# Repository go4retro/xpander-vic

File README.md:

# X-Pander VIC

## Introduction

Cousin to the X-Pander 3 for the C64/SX/C128/C128D, X-Pander VIC opens up a wealth of expansion options for your Commodore VIC-20/VIC-1001. This design continues on tradition of vintage designs like the CardCo Cardboard, while adding more granular controls over select lines like the CMD EX-3/EX2+1 for the C64. The X-Pander VIC offers the following features:

- Individually-selectable expansion ports
- sPower indicators for each port
- Ability to swap IO select lines ports
- Easily accessed piano-style configuration switches
- Top-loading or back-loading terminal port.
- Terminal port can accommodate 2 cartridges at the same time*
- Reset switch

\* Both top and back-loading options for terminal port share a single set of configuration switches, requiring 2 cartridges that can coexist without configuration.

## Requirements

- Commodore VIC-20 or VIC-1001

## Purchase

The current X-Pander VIC design is not yet available, but an older model (which requires some modification by the consumer can be purchased at the [RETRO Innovations Online Store](https://store.go4retro.com/non-functional-goodies/).

## Technical Details

X-Pander VIC creates a “passive” cartridge port “bus”, with switches on the following lines:

- Power (2 switches)
- IO2
- IO3
- RAM1
- RAM2
- RAM3
- BLK1
- BLK2
- BLK3
- BLK5
- AUDIO

Additionally, all ports except the first contain jumpers allowing one to “swap”  IO2 and IO3. This can be used to move a peripheral cartridge (like a  serial card or ethernet card) normally residing at IO3 to the  alternative IO3 position so that it can coexist with another IO cartridge. Jumpers are provided, but the jumper  pins can be removed and replaced with a subminiature DPDT (double pole,  double throw) switch.

## Support

Expansion port cartridges were not normally designed to coexist with  other cartridges. Thus, it is impossible to detail the nearly infinite  combinations and whether each works or not. Also, since the “bus”  places additional load on the unbuffered expansion port IO lines,  cartridges that are susceptible to signal degradation may not work with  X-Pander VIC, even when installed alone.

Some helpful hints:

- Always insert or remove X-Pander VIC with the system port off
- Clean cartridge contacts before installation
- Switches are “on” when depressed. Normally, all switches can be left in the “on” position
- IO2/IO3 swap jumpers must be moved as a pairs

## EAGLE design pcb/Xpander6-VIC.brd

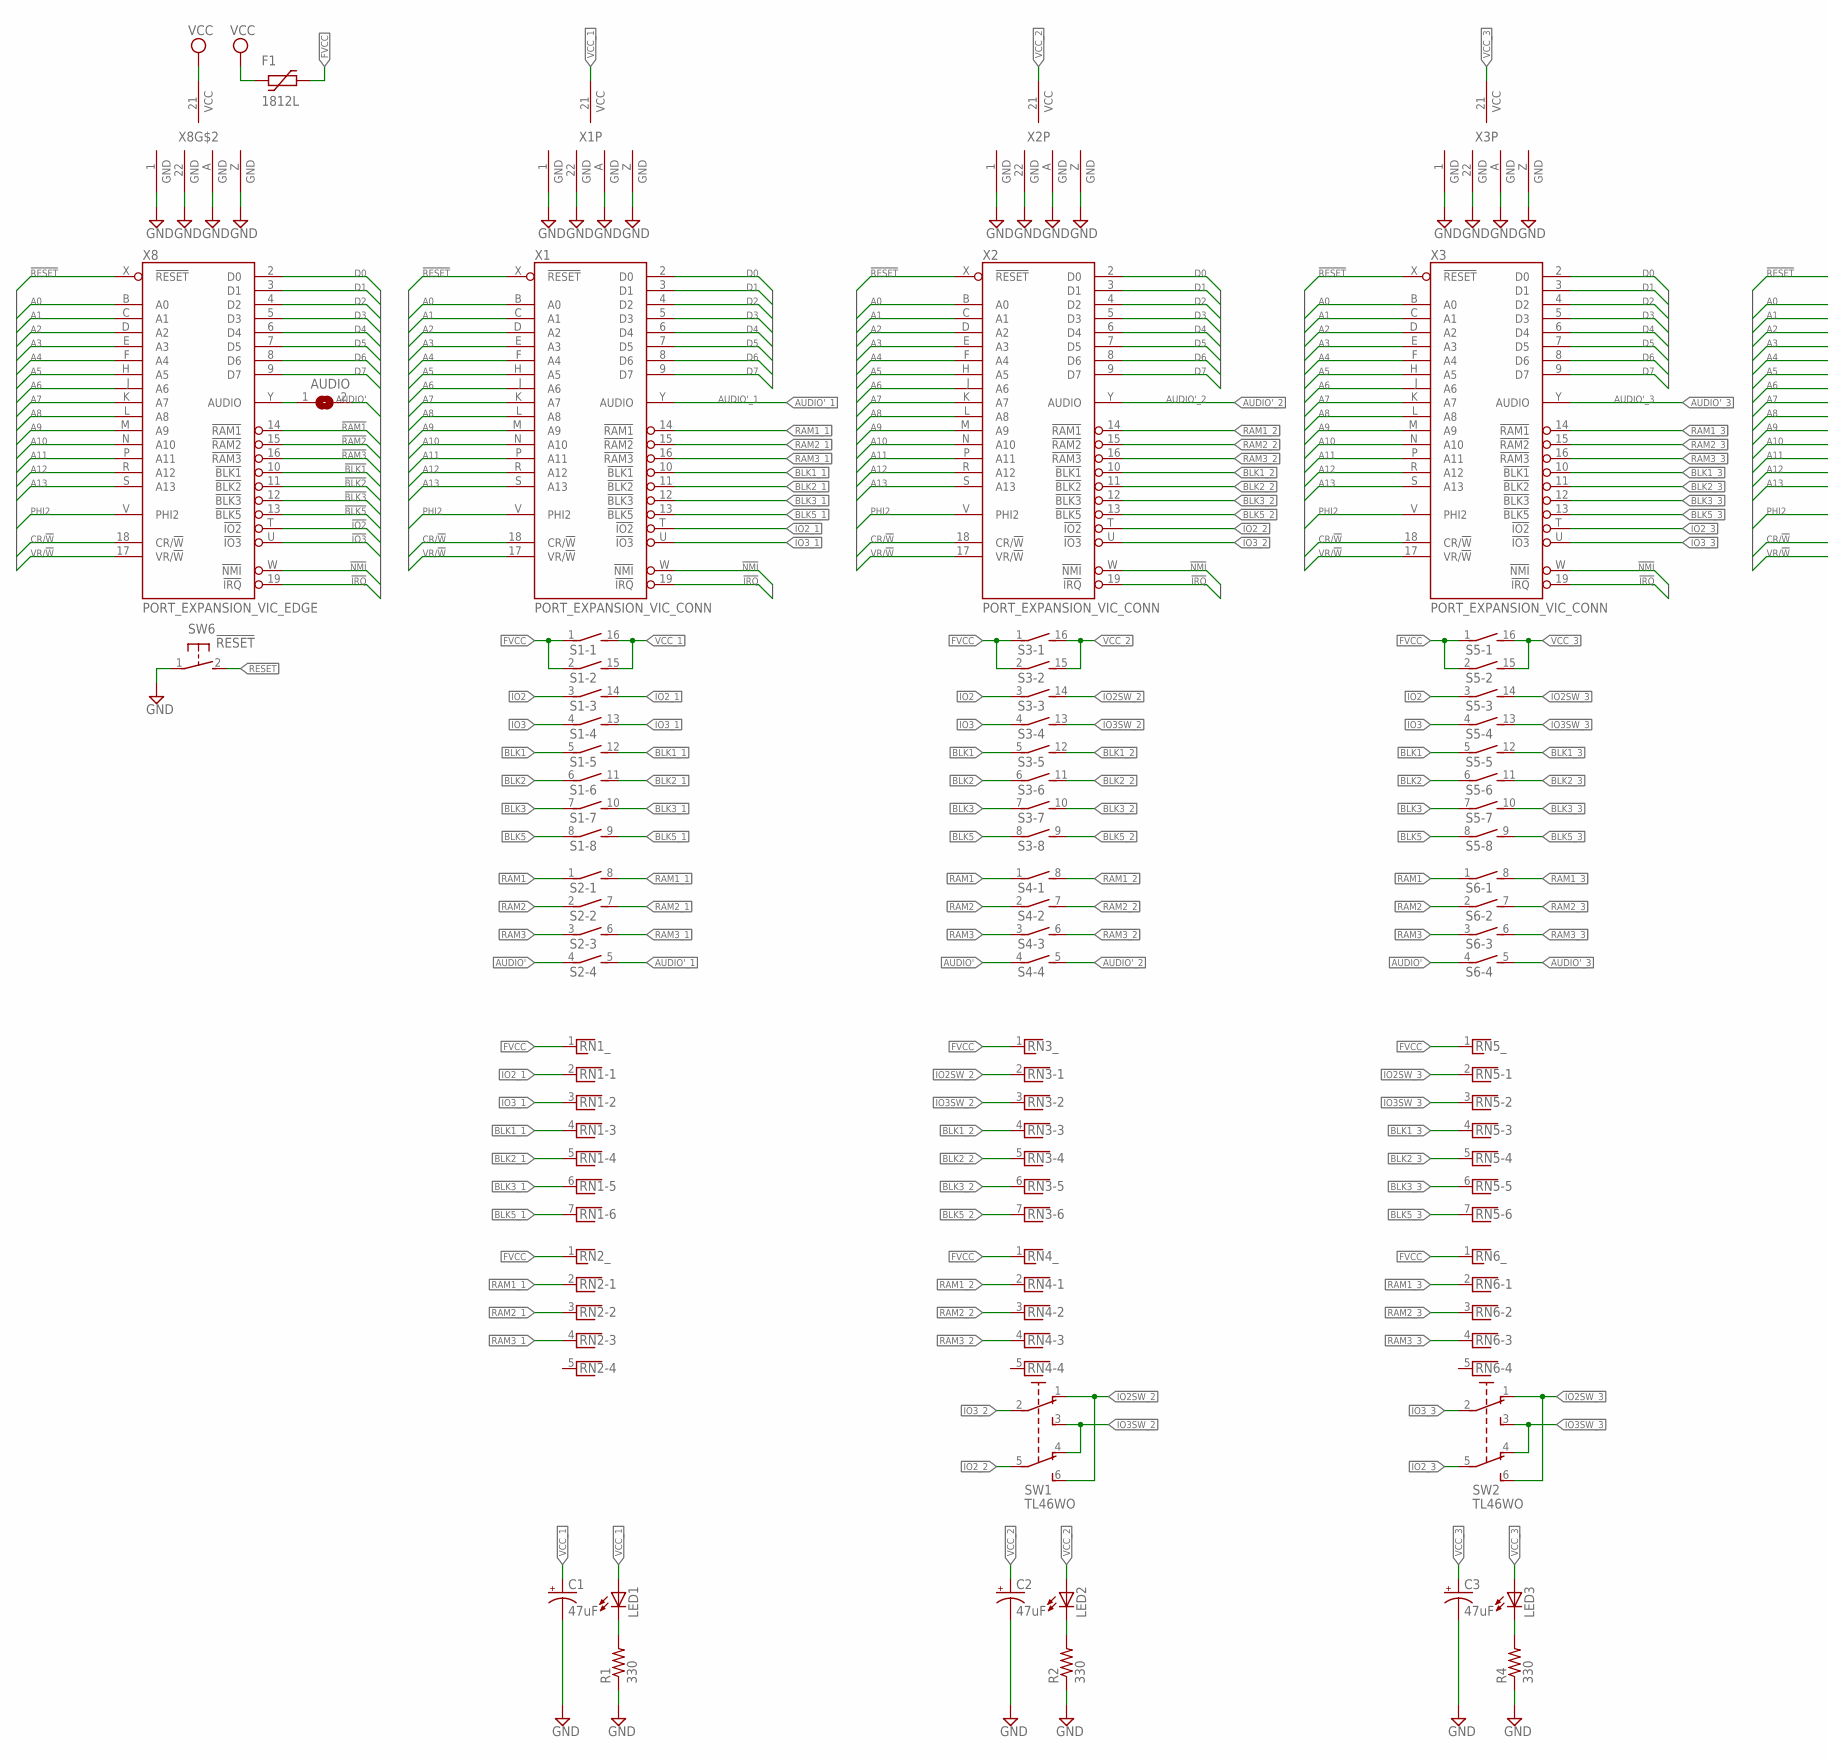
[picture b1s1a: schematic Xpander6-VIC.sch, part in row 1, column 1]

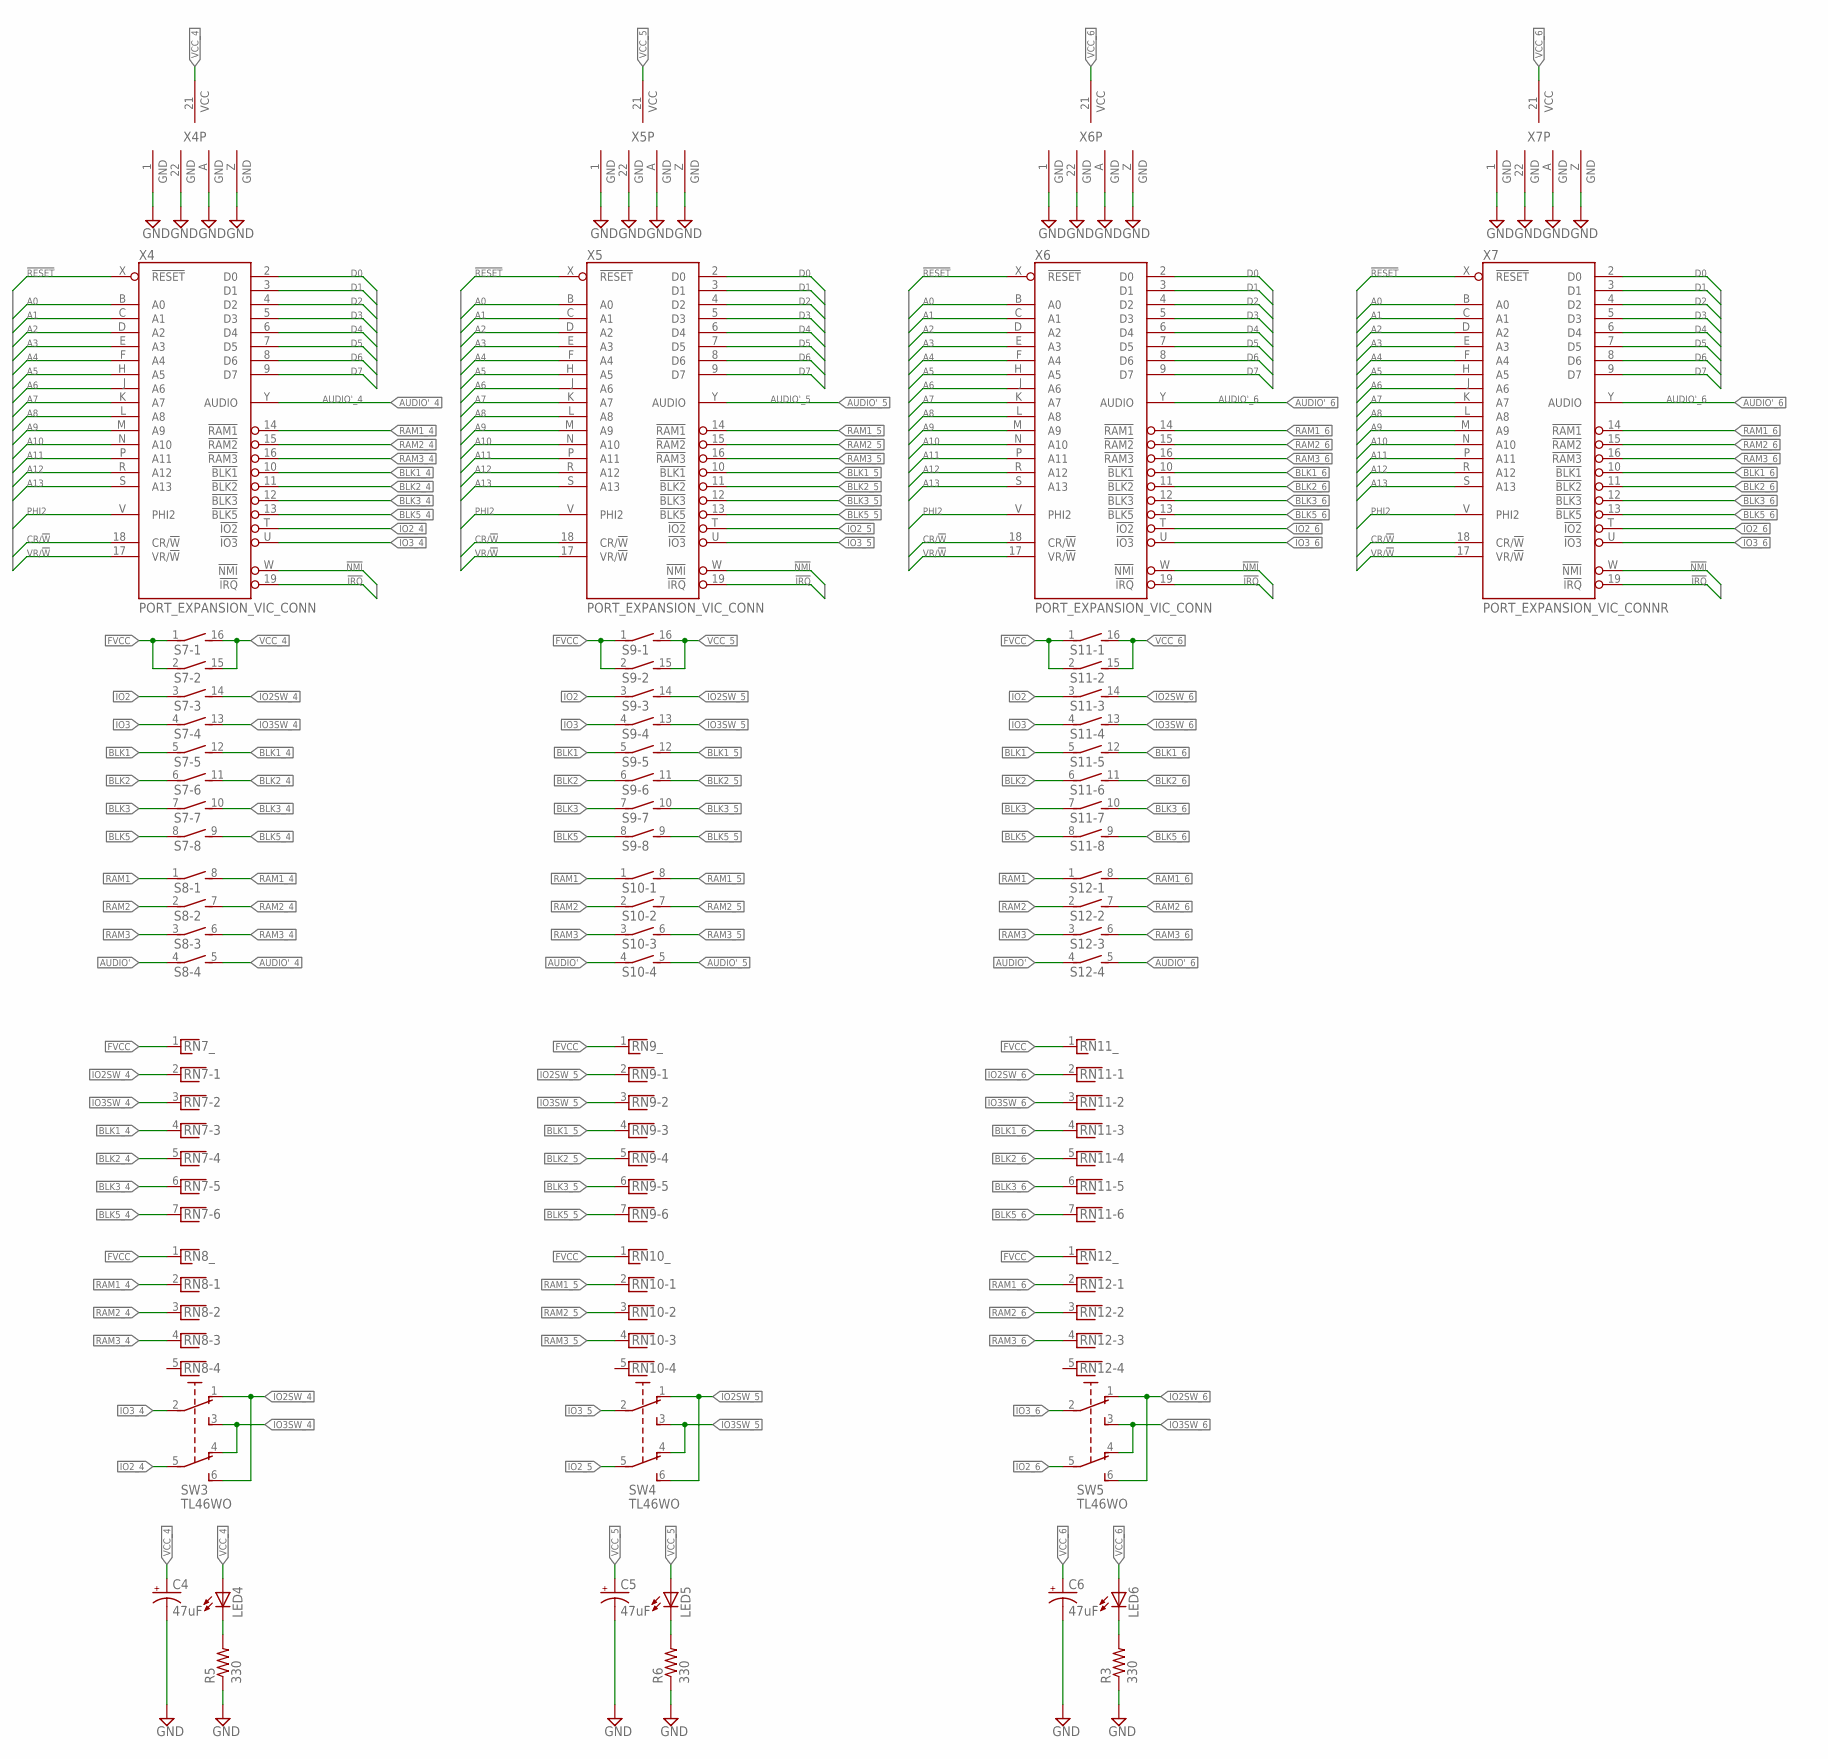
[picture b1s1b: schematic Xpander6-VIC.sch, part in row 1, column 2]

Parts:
AUDIO: SJ
C1, C2, C3, C4, C5, C6: 47uF; E2,5-6E
F1: 1812L
LED1, LED2, LED3, LED4, LED5, LED6: LED3MM
R1, R2, R3, R4, R5, R6: 330; 0204/7
RN1, RN3, RN5, RN7, RN9, RN11: RNX6; RN-7
RN2, RN4, RN6, RN8, RN10, RN12: RNX4; RN-5
S1, S3, S5, S7, S9, S11: DIP08SB
S2, S4, S6, S8, S10, S12: DIP04SB
SW1, SW2, SW3, SW4, SW5: TL46WO; TL4XWO
SW6: !RESET; B3F-31XX
X1, X2, X3, X4, X5, X6: PORT_EXPANSION_VIC_CONN; FE156-22-2
X7: PORT_EXPANSION_VIC_CONNR; MA156-22-2SHORT
X8: PORT_EXPANSION_VIC_EDGE; MA156-22-2

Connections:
!BLK1: S1.5 (1), S3.5 (1), S5.5 (1), S7.5 (1), S9.5 (1), S11.5 (1), X8.10 (!BLK1)
!BLK1_1: RN1.4, S1.12 (2), X1.10 (!BLK1)
!BLK1_2: RN3.4, S3.12 (2), X2.10 (!BLK1)
!BLK1_3: RN5.4, S5.12 (2), X3.10 (!BLK1)
!BLK1_4: RN7.4, S7.12 (2), X4.10 (!BLK1)
!BLK1_5: RN9.4, S9.12 (2), X5.10 (!BLK1)
!BLK1_6: RN11.4, S11.12 (2), X6.10 (!BLK1), X7.10 (!BLK1)
!BLK2: S1.6 (1), S3.6 (1), S5.6 (1), S7.6 (1), S9.6 (1), S11.6 (1), X8.11 (!BLK2)
!BLK2_1: RN1.5, S1.11 (2), X1.11 (!BLK2)
!BLK2_2: RN3.5, S3.11 (2), X2.11 (!BLK2)
!BLK2_3: RN5.5, S5.11 (2), X3.11 (!BLK2)
!BLK2_4: RN7.5, S7.11 (2), X4.11 (!BLK2)
!BLK2_5: RN9.5, S9.11 (2), X5.11 (!BLK2)
!BLK2_6: RN11.5, S11.11 (2), X6.11 (!BLK2), X7.11 (!BLK2)
!BLK3: S1.7 (1), S3.7 (1), S5.7 (1), S7.7 (1), S9.7 (1), S11.7 (1), X8.12 (!BLK3)
!BLK3_1: RN1.6, S1.10 (2), X1.12 (!BLK3)
!BLK3_2: RN3.6, S3.10 (2), X2.12 (!BLK3)
!BLK3_3: RN5.6, S5.10 (2), X3.12 (!BLK3)
!BLK3_4: RN7.6, S7.10 (2), X4.12 (!BLK3)
!BLK3_5: RN9.6, S9.10 (2), X5.12 (!BLK3)
!BLK3_6: RN11.6, S11.10 (2), X6.12 (!BLK3), X7.12 (!BLK3)
!BLK5: S1.8 (1), S3.8 (1), S5.8 (1), S7.8 (1), S9.8 (1), S11.8 (1), X8.13 (!BLK5)
!BLK5_1: RN1.7, S1.9 (2), X1.13 (!BLK5)
!BLK5_2: RN3.7, S3.9 (2), X2.13 (!BLK5)
!BLK5_3: RN5.7, S5.9 (2), X3.13 (!BLK5)
!BLK5_4: RN7.7, S7.9 (2), X4.13 (!BLK5)
!BLK5_5: RN9.7, S9.9 (2), X5.13 (!BLK5)
!BLK5_6: RN11.7, S11.9 (2), X6.13 (!BLK5), X7.13 (!BLK5)
!IO2: S1.3 (1), S3.3 (1), S5.3 (1), S7.3 (1), S9.3 (1), S11.3 (1), X8.T (!IO2)
!IO2SW_2: RN3.2, S3.14 (2), SW1.1 (O), SW1.6 (S1)
!IO2SW_3: RN5.2, S5.14 (2), SW2.1 (O), SW2.6 (S1)
!IO2SW_4: RN7.2, S7.14 (2), SW3.1 (O), SW3.6 (S1)
!IO2SW_5: RN9.2, S9.14 (2), SW4.1 (O), SW4.6 (S1)
!IO2SW_6: RN11.2, S11.14 (2), SW5.1 (O), SW5.6 (S1)
!IO2_1: RN1.2, S1.14 (2), X1.T (!IO2)
!IO2_2: SW1.5 (P1), X2.T (!IO2)
!IO2_3: SW2.5 (P1), X3.T (!IO2)
!IO2_4: SW3.5 (P1), X4.T (!IO2)
!IO2_5: SW4.5 (P1), X5.T (!IO2)
!IO2_6: SW5.5 (P1), X6.T (!IO2), X7.T (!IO2)
!IO3: S1.4 (1), S3.4 (1), S5.4 (1), S7.4 (1), S9.4 (1), S11.4 (1), X8.U (!IO3)
!IO3SW_2: RN3.3, S3.13 (2), SW1.3 (S), SW1.4 (O1)
!IO3SW_3: RN5.3, S5.13 (2), SW2.3 (S), SW2.4 (O1)
!IO3SW_4: RN7.3, S7.13 (2), SW3.3 (S), SW3.4 (O1)
!IO3SW_5: RN9.3, S9.13 (2), SW4.3 (S), SW4.4 (O1)
!IO3SW_6: RN11.3, S11.13 (2), SW5.3 (S), SW5.4 (O1)
!IO3_1: RN1.3, S1.13 (2), X1.U (!IO3)
!IO3_2: SW1.2, X2.U (!IO3)
!IO3_3: SW2.2, X3.U (!IO3)
!IO3_4: SW3.2, X4.U (!IO3)
!IO3_5: SW4.2, X5.U (!IO3)
!IO3_6: SW5.2, X6.U (!IO3), X7.U (!IO3)
!IRQ: X1.19 (!IRQ), X2.19 (!IRQ), X3.19 (!IRQ), X4.19 (!IRQ), X5.19 (!IRQ), X6.19 (!IRQ), X7.19 (!IRQ), X8.19 (!IRQ)
!NMI: X1.W (!NMI), X2.W (!NMI), X3.W (!NMI), X4.W (!NMI), X5.W (!NMI), X6.W (!NMI), X7.W (!NMI), X8.W (!NMI)
!RAM1: S2.1, S4.1, S6.1, S8.1, S10.1, S12.1, X8.14 (!RAM1)
!RAM1_1: RN2.2, S2.8 (2), X1.14 (!RAM1)
!RAM1_2: RN4.2, S4.8 (2), X2.14 (!RAM1)
!RAM1_3: RN6.2, S6.8 (2), X3.14 (!RAM1)
!RAM1_4: RN8.2, S8.8 (2), X4.14 (!RAM1)
!RAM1_5: RN10.2, S10.8 (2), X5.14 (!RAM1)
!RAM1_6: RN12.2, S12.8 (2), X6.14 (!RAM1), X7.14 (!RAM1)
!RAM2: S2.2 (1), S4.2 (1), S6.2 (1), S8.2 (1), S10.2 (1), S12.2 (1), X8.15 (!RAM2)
!RAM2_1: RN2.3, S2.7 (2), X1.15 (!RAM2)
!RAM2_2: RN4.3, S4.7 (2), X2.15 (!RAM2)
!RAM2_3: RN6.3, S6.7 (2), X3.15 (!RAM2)
!RAM2_4: RN8.3, S8.7 (2), X4.15 (!RAM2)
!RAM2_5: RN10.3, S10.7 (2), X5.15 (!RAM2)
!RAM2_6: RN12.3, S12.7 (2), X6.15 (!RAM2), X7.15 (!RAM2)
!RAM3: S2.3 (1), S4.3 (1), S6.3 (1), S8.3 (1), S10.3 (1), S12.3 (1), X8.16 (!RAM3)
!RAM3_1: RN2.4, S2.6 (2), X1.16 (!RAM3)
!RAM3_2: RN4.4, S4.6 (2), X2.16 (!RAM3)
!RAM3_3: RN6.4, S6.6 (2), X3.16 (!RAM3)
!RAM3_4: RN8.4, S8.6 (2), X4.16 (!RAM3)
!RAM3_5: RN10.4, S10.6 (2), X5.16 (!RAM3)
!RAM3_6: RN12.4, S12.6 (2), X6.16 (!RAM3), X7.16 (!RAM3)
!RESET: SW6.2 (S), X1.X (!RESET), X2.X (!RESET), X3.X (!RESET), X4.X (!RESET), X5.X (!RESET), X6.X (!RESET), X7.X (!RESET), X8.X (!RESET)
A0: X1.B (A0), X2.B (A0), X3.B (A0), X4.B (A0), X5.B (A0), X6.B (A0), X7.B (A0), X8.B (A0)
A1: X1.C (A1), X2.C (A1), X3.C (A1), X4.C (A1), X5.C (A1), X6.C (A1), X7.C (A1), X8.C (A1)
A2: X1.D (A2), X2.D (A2), X3.D (A2), X4.D (A2), X5.D (A2), X6.D (A2), X7.D (A2), X8.D (A2)
A3: X1.E (A3), X2.E (A3), X3.E (A3), X4.E (A3), X5.E (A3), X6.E (A3), X7.E (A3), X8.E (A3)
A4: X1.F (A4), X2.F (A4), X3.F (A4), X4.F (A4), X5.F (A4), X6.F (A4), X7.F (A4), X8.F (A4)
A5: X1.H (A5), X2.H (A5), X3.H (A5), X4.H (A5), X5.H (A5), X6.H (A5), X7.H (A5), X8.H (A5)
A6: X1.J (A6), X2.J (A6), X3.J (A6), X4.J (A6), X5.J (A6), X6.J (A6), X7.J (A6), X8.J (A6)
A7: X1.K (A7), X2.K (A7), X3.K (A7), X4.K (A7), X5.K (A7), X6.K (A7), X7.K (A7), X8.K (A7)
A8: X1.L (A8), X2.L (A8), X3.L (A8), X4.L (A8), X5.L (A8), X6.L (A8), X7.L (A8), X8.L (A8)
A9: X1.M (A9), X2.M (A9), X3.M (A9), X4.M (A9), X5.M (A9), X6.M (A9), X7.M (A9), X8.M (A9)
A10: X1.N (A10), X2.N (A10), X3.N (A10), X4.N (A10), X5.N (A10), X6.N (A10), X7.N (A10), X8.N (A10)
A11: X1.P (A11), X2.P (A11), X3.P (A11), X4.P (A11), X5.P (A11), X6.P (A11), X7.P (A11), X8.P (A11)
A12: X1.R (A12), X2.R (A12), X3.R (A12), X4.R (A12), X5.R (A12), X6.R (A12), X7.R (A12), X8.R (A12)
A13: X1.S (A13), X2.S (A13), X3.S (A13), X4.S (A13), X5.S (A13), X6.S (A13), X7.S (A13), X8.S (A13)
AUDIO: AUDIO.1, X8.Y (AUDIO)
AUDIO': AUDIO.2, S2.4 (1), S4.4 (1), S6.4 (1), S8.4 (1), S10.4 (1), S12.4 (1)
AUDIO'_1: S2.5 (2), X1.Y (AUDIO)
AUDIO'_2: S4.5 (2), X2.Y (AUDIO)
AUDIO'_3: S6.5 (2), X3.Y (AUDIO)
AUDIO'_4: S8.5 (2), X4.Y (AUDIO)
AUDIO'_5: S10.5 (2), X5.Y (AUDIO)
AUDIO'_6: S12.5 (2), X6.Y (AUDIO), X7.Y (AUDIO)
CR/!W: X1.18 (CR/!W), X2.18 (CR/!W), X3.18 (CR/!W), X4.18 (CR/!W), X5.18 (CR/!W), X6.18 (CR/!W), X7.18 (CR/!W), X8.18 (CR/!W)
D0: X1.2 (D0), X2.2 (D0), X3.2 (D0), X4.2 (D0), X5.2 (D0), X6.2 (D0), X7.2 (D0), X8.2 (D0)
D1: X1.3 (D1), X2.3 (D1), X3.3 (D1), X4.3 (D1), X5.3 (D1), X6.3 (D1), X7.3 (D1), X8.3 (D1)
D2: X1.4 (D2), X2.4 (D2), X3.4 (D2), X4.4 (D2), X5.4 (D2), X6.4 (D2), X7.4 (D2), X8.4 (D2)
D3: X1.5 (D3), X2.5 (D3), X3.5 (D3), X4.5 (D3), X5.5 (D3), X6.5 (D3), X7.5 (D3), X8.5 (D3)
D4: X1.6 (D4), X2.6 (D4), X3.6 (D4), X4.6 (D4), X5.6 (D4), X6.6 (D4), X7.6 (D4), X8.6 (D4)
D5: X1.7 (D5), X2.7 (D5), X3.7 (D5), X4.7 (D5), X5.7 (D5), X6.7 (D5), X7.7 (D5), X8.7 (D5)
D6: X1.8 (D6), X2.8 (D6), X3.8 (D6), X4.8 (D6), X5.8 (D6), X6.8 (D6), X7.8 (D6), X8.8 (D6)
D7: X1.9 (D7), X2.9 (D7), X3.9 (D7), X4.9 (D7), X5.9 (D7), X6.9 (D7), X7.9 (D7), X8.9 (D7)
FVCC: F1.P$2 (2), RN1.1, RN2.1, RN3.1, RN4.1, RN5.1, RN6.1, RN7.1, RN8.1, RN9.1, RN10.1, RN11.1, RN12.1, S1.1, S1.2 (1), S3.1, S3.2 (1), S5.1, S5.2 (1), S7.1, S7.2 (1), S9.1, S9.2 (1), S11.1, S11.2 (1)
GND: C1.-, C2.-, C3.-, C4.-, C5.-, C6.-, R1.1, R2.1, R3.1, R4.1, R5.1, R6.1, SW6.1, X1.1 (GND), X1.22 (GND), X1.A (GND), X1.Z (GND), X2.1 (GND), X2.22 (GND), X2.A (GND), X2.Z (GND), X3.1 (GND), X3.22 (GND), X3.A (GND), X3.Z (GND), X4.1 (GND), X4.22 (GND), X4.A (GND), X4.Z (GND), X5.1 (GND), X5.22 (GND), X5.A (GND), X5.Z (GND), X6.1 (GND), X6.22 (GND), X6.A (GND), X6.Z (GND), X7.1 (GND), X7.22 (GND), X7.A (GND), X7.Z (GND), X8.1 (GND), X8.22 (GND), X8.A (GND), X8.Z (GND)
unnamed: LED1.K (C), R1.2
unnamed: LED2.K (C), R2.2
unnamed: LED6.K (C), R3.2
unnamed: LED3.K (C), R4.2
unnamed: LED4.K (C), R5.2
unnamed: LED5.K (C), R6.2
PHI2: X1.V (PHI2), X2.V (PHI2), X3.V (PHI2), X4.V (PHI2), X5.V (PHI2), X6.V (PHI2), X7.V (PHI2), X8.V (PHI2)
VCC: F1.P$1 (1), X8.21 (VCC)
VCC_1: C1.+, LED1.A, S1.15 (2), S1.16 (2), X1.21 (VCC)
VCC_2: C2.+, LED2.A, S3.15 (2), S3.16 (2), X2.21 (VCC)
VCC_3: C3.+, LED3.A, S5.15 (2), S5.16 (2), X3.21 (VCC)
VCC_4: C4.+, LED4.A, S7.15 (2), S7.16 (2), X4.21 (VCC)
VCC_5: C5.+, LED5.A, S9.15 (2), S9.16 (2), X5.21 (VCC)
VCC_6: C6.+, LED6.A, S11.15 (2), S11.16 (2), X6.21 (VCC), X7.21 (VCC)
VR/!W: X1.17 (VR/!W), X2.17 (VR/!W), X3.17 (VR/!W), X4.17 (VR/!W), X5.17 (VR/!W), X6.17 (VR/!W), X7.17 (VR/!W), X8.17 (VR/!W)

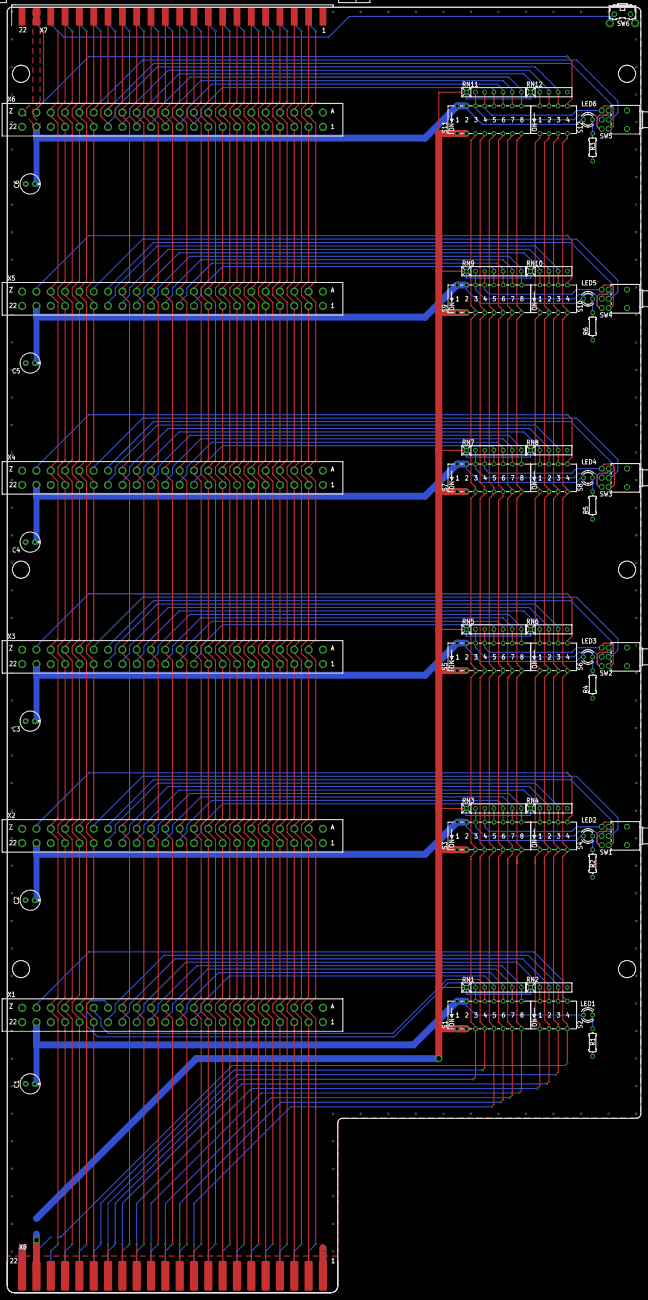
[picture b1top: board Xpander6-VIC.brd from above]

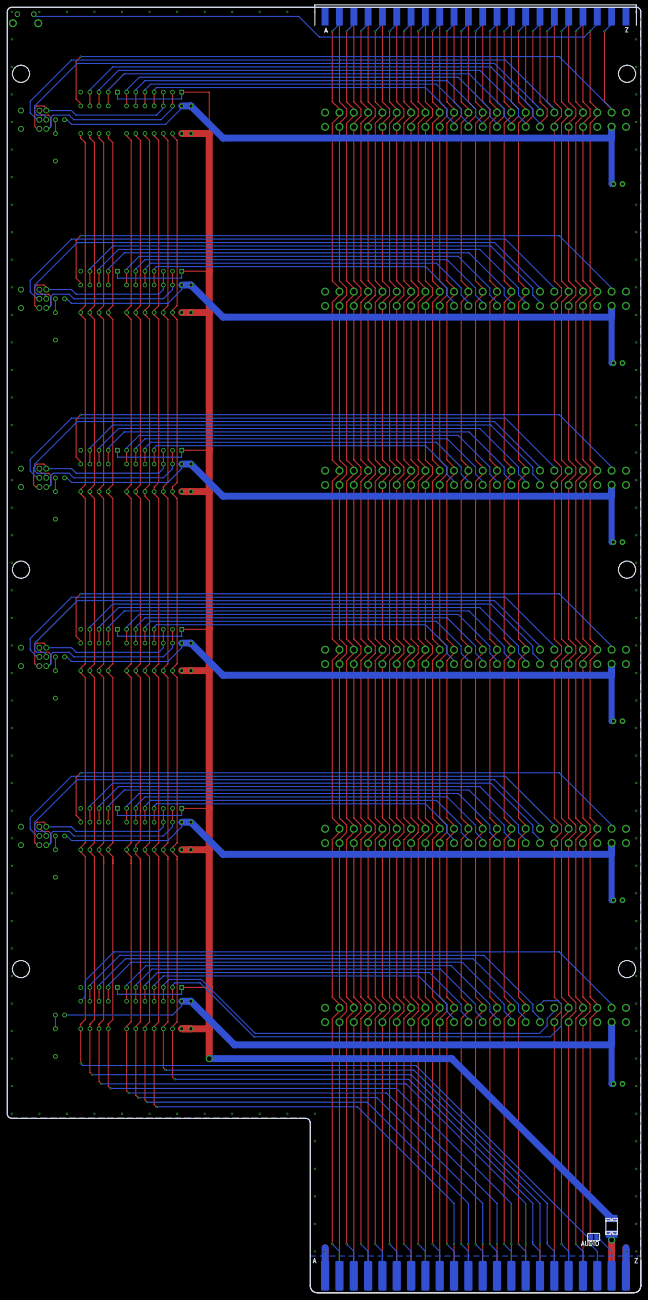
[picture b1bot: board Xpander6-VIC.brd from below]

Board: 2 copper layers, 175.3 x 355.6 mm, 58 parts (2 on the bottom side), 124 nets.

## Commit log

2024-04-21 Update license
2024-04-21 v1 design
2024-04-21 v1.1 design (switches are still too close)
2024-04-21 Add 6 slot variant (still need to reduce slot pitch)
2024-04-21 Convert 6 slot design to use newer symbols
2024-04-21 Route optional audio line
2024-04-21 Add images
2024-04-21 Add README.md
2024-05-01 More updates
2024-05-01 Updated pics
